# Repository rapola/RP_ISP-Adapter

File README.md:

# RP_ISP-Adapter

<br>
### Schematic
#### https://github.com/rapola/RP_ISP-Adapter/blob/main/V1.0/ISP_Adapter_V10.pdf
---
#### ordered 10pcs (JLCPCB), delivered Jan 2021

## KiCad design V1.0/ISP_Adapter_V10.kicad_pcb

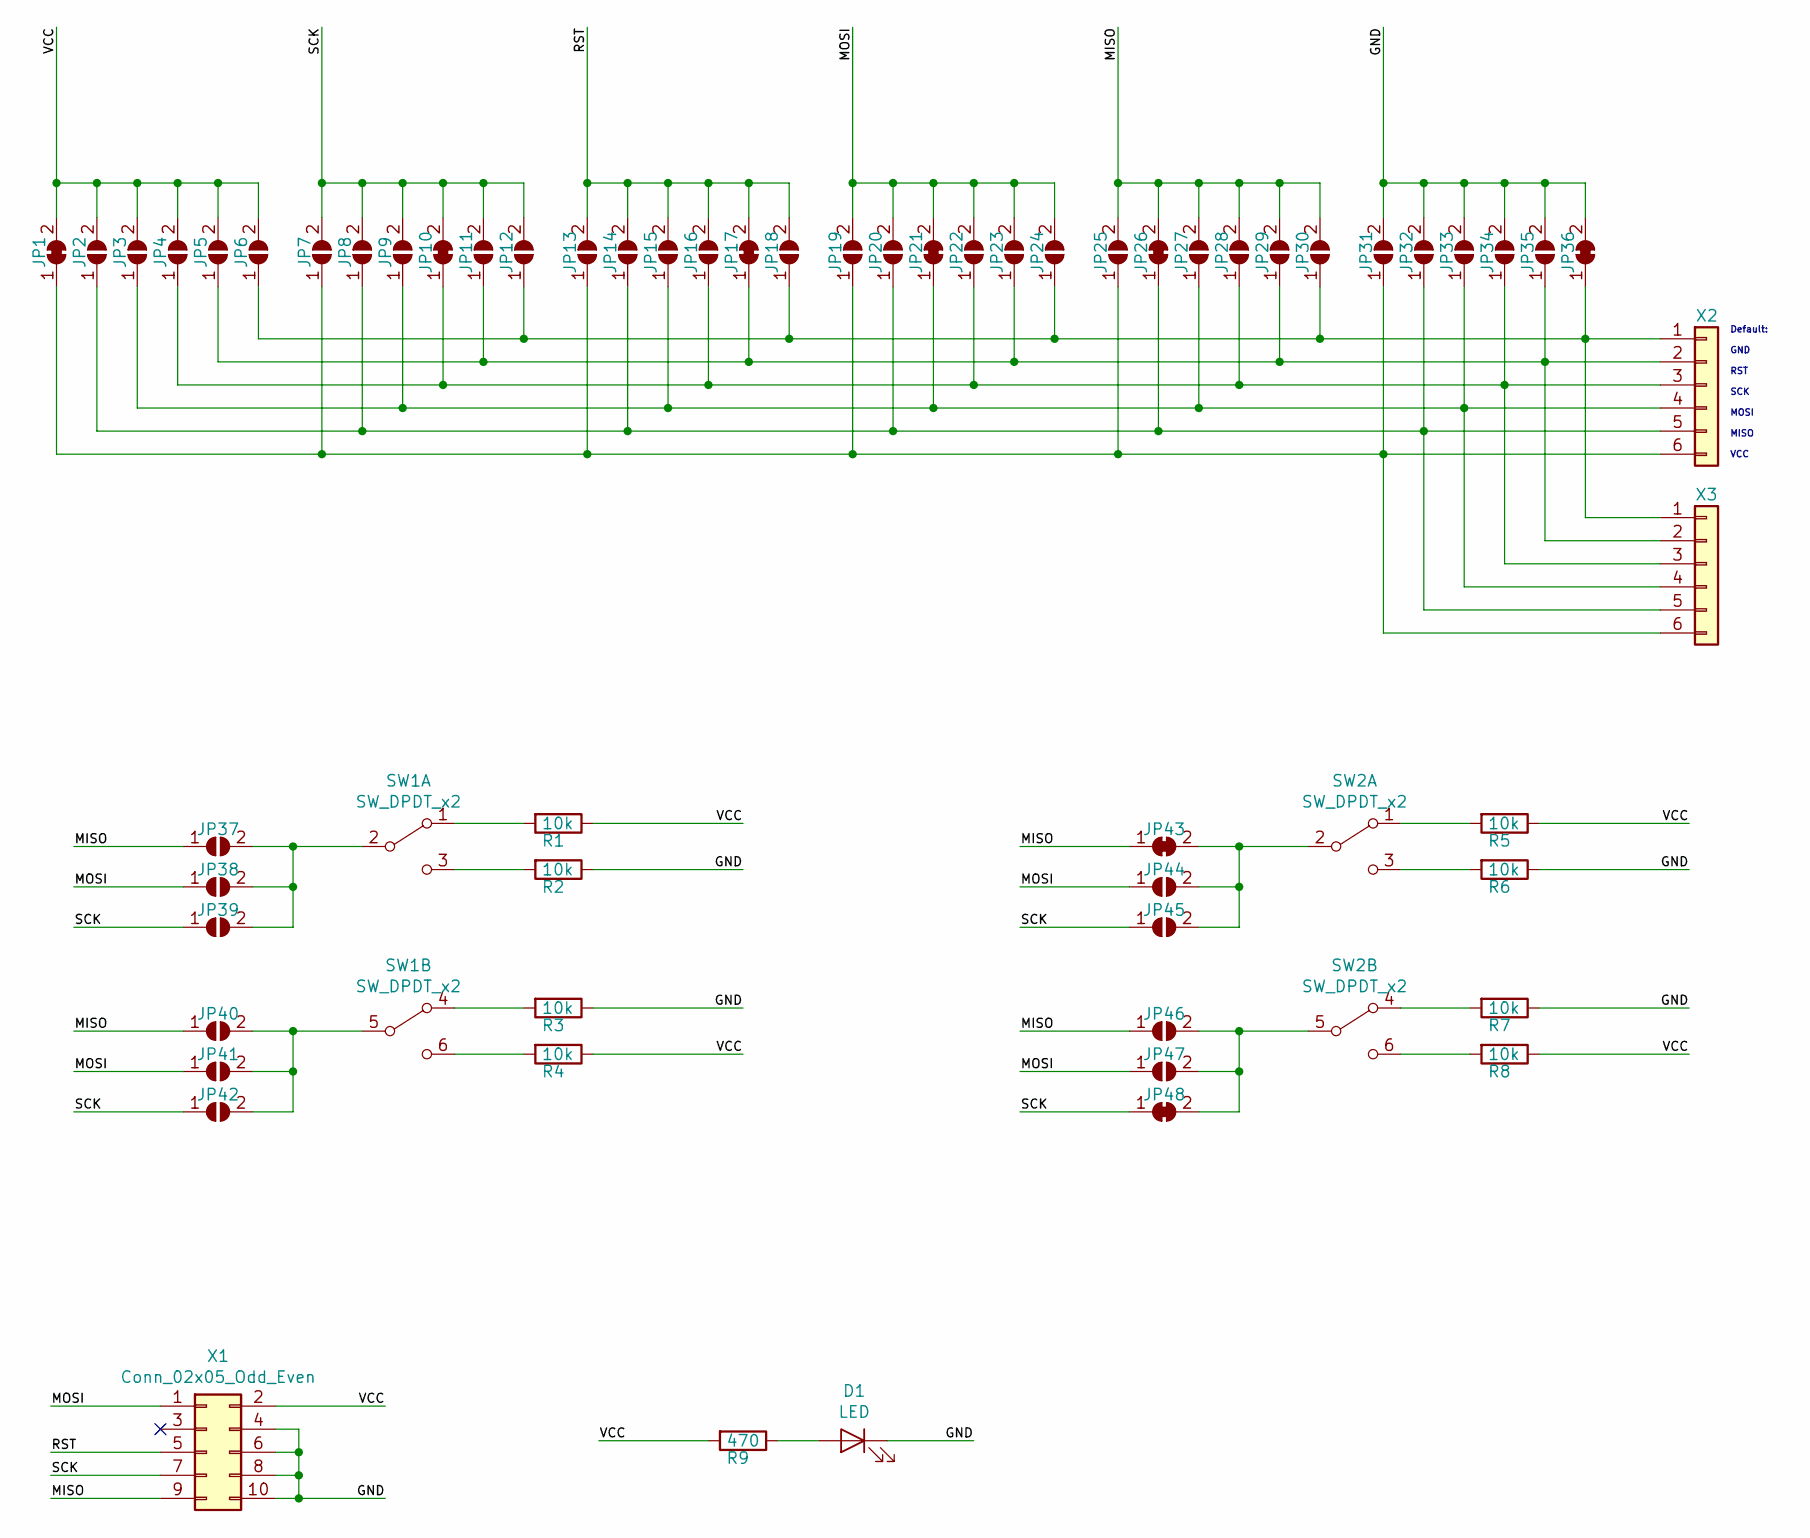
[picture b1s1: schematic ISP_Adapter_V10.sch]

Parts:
D1: LED; LED_0805_2012Metric
JP1, JP10, JP17, JP21, JP26, JP36, JP43, JP48: SolderJumper_2_Bridged; SolderJumper-2_P1.3mm_Bridged_RoundedPad1.0x1.5mm
JP2, JP3, JP4, JP5, JP6, JP7, JP8, JP9, JP11, JP12, JP13, JP14, JP15, JP16, JP18, JP19, JP20, JP22, JP23, JP24, JP25, JP27, JP28, JP29, JP30, JP31, JP32, JP33, JP34, JP35, JP37, JP38, JP39, JP40, JP41, JP42, JP44, JP45, JP46, JP47: SolderJumper_2_Open; SolderJumper-2_P1.3mm_Open_RoundedPad1.0x1.5mm
R1, R2, R3, R4, R5, R6, R7, R8: 10k; R_0805_2012Metric
R9: 470; R_0805_2012Metric
SW1, SW2: SW_DPDT_x2; SW_CuK_JS202011CQN_DPDT_Straight
X1: Conn_02x05_Odd_Even; IDC-Header_2x05_P2.54mm_Vertical
X2: Conn_01x06; Molex_PicoBlade_53398-0671_1x06-1MP_P1.25mm_Vertical
X3: Conn_01x06; PinHeader_1x06_P2.54mm_Vertical

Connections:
/GND: D1.1 (K), JP31.2 (B), JP32.2 (B), JP33.2 (B), JP34.2 (B), JP35.2 (B), JP36.2 (B), R2.1, R3.1, R6.1, R7.1, X1.4, X1.6, X1.8, X1.10
/MISO: JP25.2 (B), JP26.2 (B), JP27.2 (B), JP28.2 (B), JP29.2 (B), JP30.2 (B), JP37.1 (A), JP40.1 (A), JP43.1 (A), JP46.1 (A), X1.9
/MOSI: JP19.2 (B), JP20.2 (B), JP21.2 (B), JP22.2 (B), JP23.2 (B), JP24.2 (B), JP38.1 (A), JP41.1 (A), JP44.1 (A), JP47.1 (A), X1.1
/RST: JP13.2 (B), JP14.2 (B), JP15.2 (B), JP16.2 (B), JP17.2 (B), JP18.2 (B), X1.5
/SCK: JP7.2 (B), JP8.2 (B), JP9.2 (B), JP10.2 (B), JP11.2 (B), JP12.2 (B), JP39.1 (A), JP42.1 (A), JP45.1 (A), JP48.1 (A), X1.7
/VCC: JP1.2 (B), JP2.2 (B), JP3.2 (B), JP4.2 (B), JP5.2 (B), JP6.2 (B), R1.1, R4.1, R5.1, R8.1, R9.2, X1.2
unnamed: D1.2 (A), R9.1
unnamed: JP1.1 (A), JP7.1 (A), JP13.1 (A), JP19.1 (A), JP25.1 (A), JP31.1 (A), X2.6, X3.6
unnamed: JP4.1 (A), JP10.1 (A), JP16.1 (A), JP22.1 (A), JP28.1 (A), JP34.1 (A), X2.3, X3.3
unnamed: JP5.1 (A), JP11.1 (A), JP17.1 (A), JP23.1 (A), JP29.1 (A), JP35.1 (A), X2.2, X3.2
unnamed: JP6.1 (A), JP12.1 (A), JP18.1 (A), JP24.1 (A), JP30.1 (A), JP36.1 (A), X2.1, X3.1
unnamed: JP2.1 (A), JP8.1 (A), JP14.1 (A), JP20.1 (A), JP26.1 (A), JP32.1 (A), X2.5, X3.5
unnamed: JP3.1 (A), JP9.1 (A), JP15.1 (A), JP21.1 (A), JP27.1 (A), JP33.1 (A), X2.4, X3.4
unnamed: JP37.2 (B), JP38.2 (B), JP39.2 (B), SW1.2 (B)
unnamed: JP40.2 (B), JP41.2 (B), JP42.2 (B), SW1.5 (B)
unnamed: JP43.2 (B), JP44.2 (B), JP45.2 (B), SW2.2 (B)
unnamed: JP46.2 (B), JP47.2 (B), JP48.2 (B), SW2.5 (B)
unnamed: R1.2, SW1.1 (A)
unnamed: R2.2, SW1.3 (C)
unnamed: R3.2, SW1.4 (A)
unnamed: R4.2, SW1.6 (C)
unnamed: R5.2, SW2.1 (A)
unnamed: R6.2, SW2.3 (C)
unnamed: R7.2, SW2.4 (A)
unnamed: R8.2, SW2.6 (C)

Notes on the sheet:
Default: GND RST SCK MOSI MISO VCC

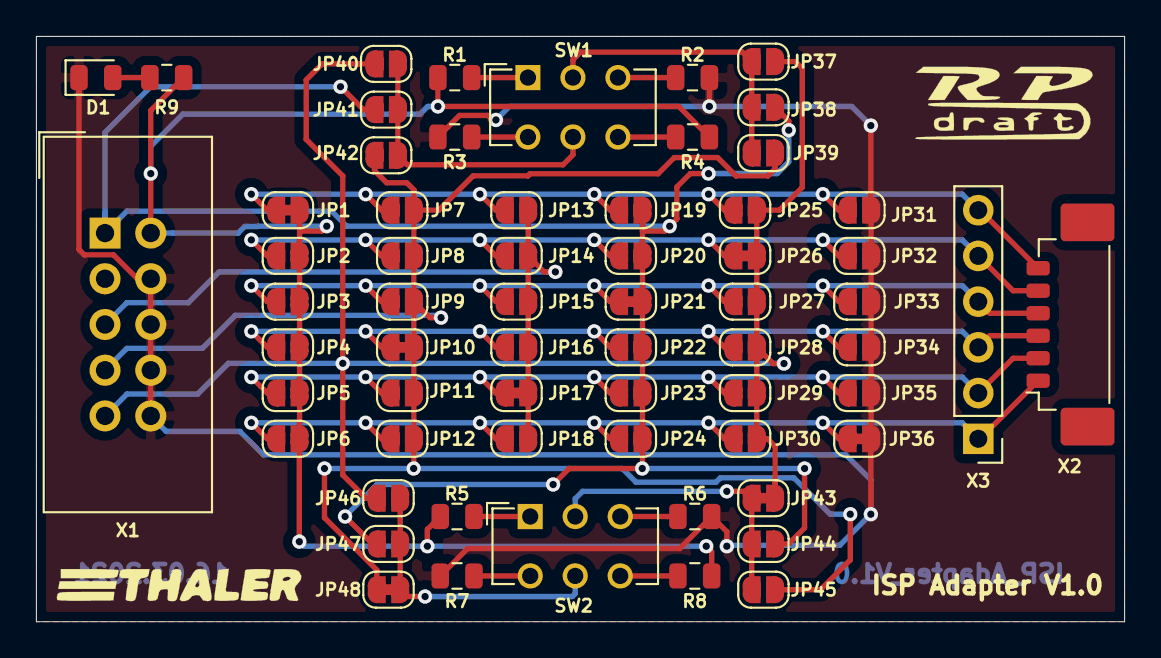
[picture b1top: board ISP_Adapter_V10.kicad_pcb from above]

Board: 2 copper layers, 60.5 x 32.5 mm, 63 parts (0 on the bottom side), 25 nets.

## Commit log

2022-09-18 initial release
